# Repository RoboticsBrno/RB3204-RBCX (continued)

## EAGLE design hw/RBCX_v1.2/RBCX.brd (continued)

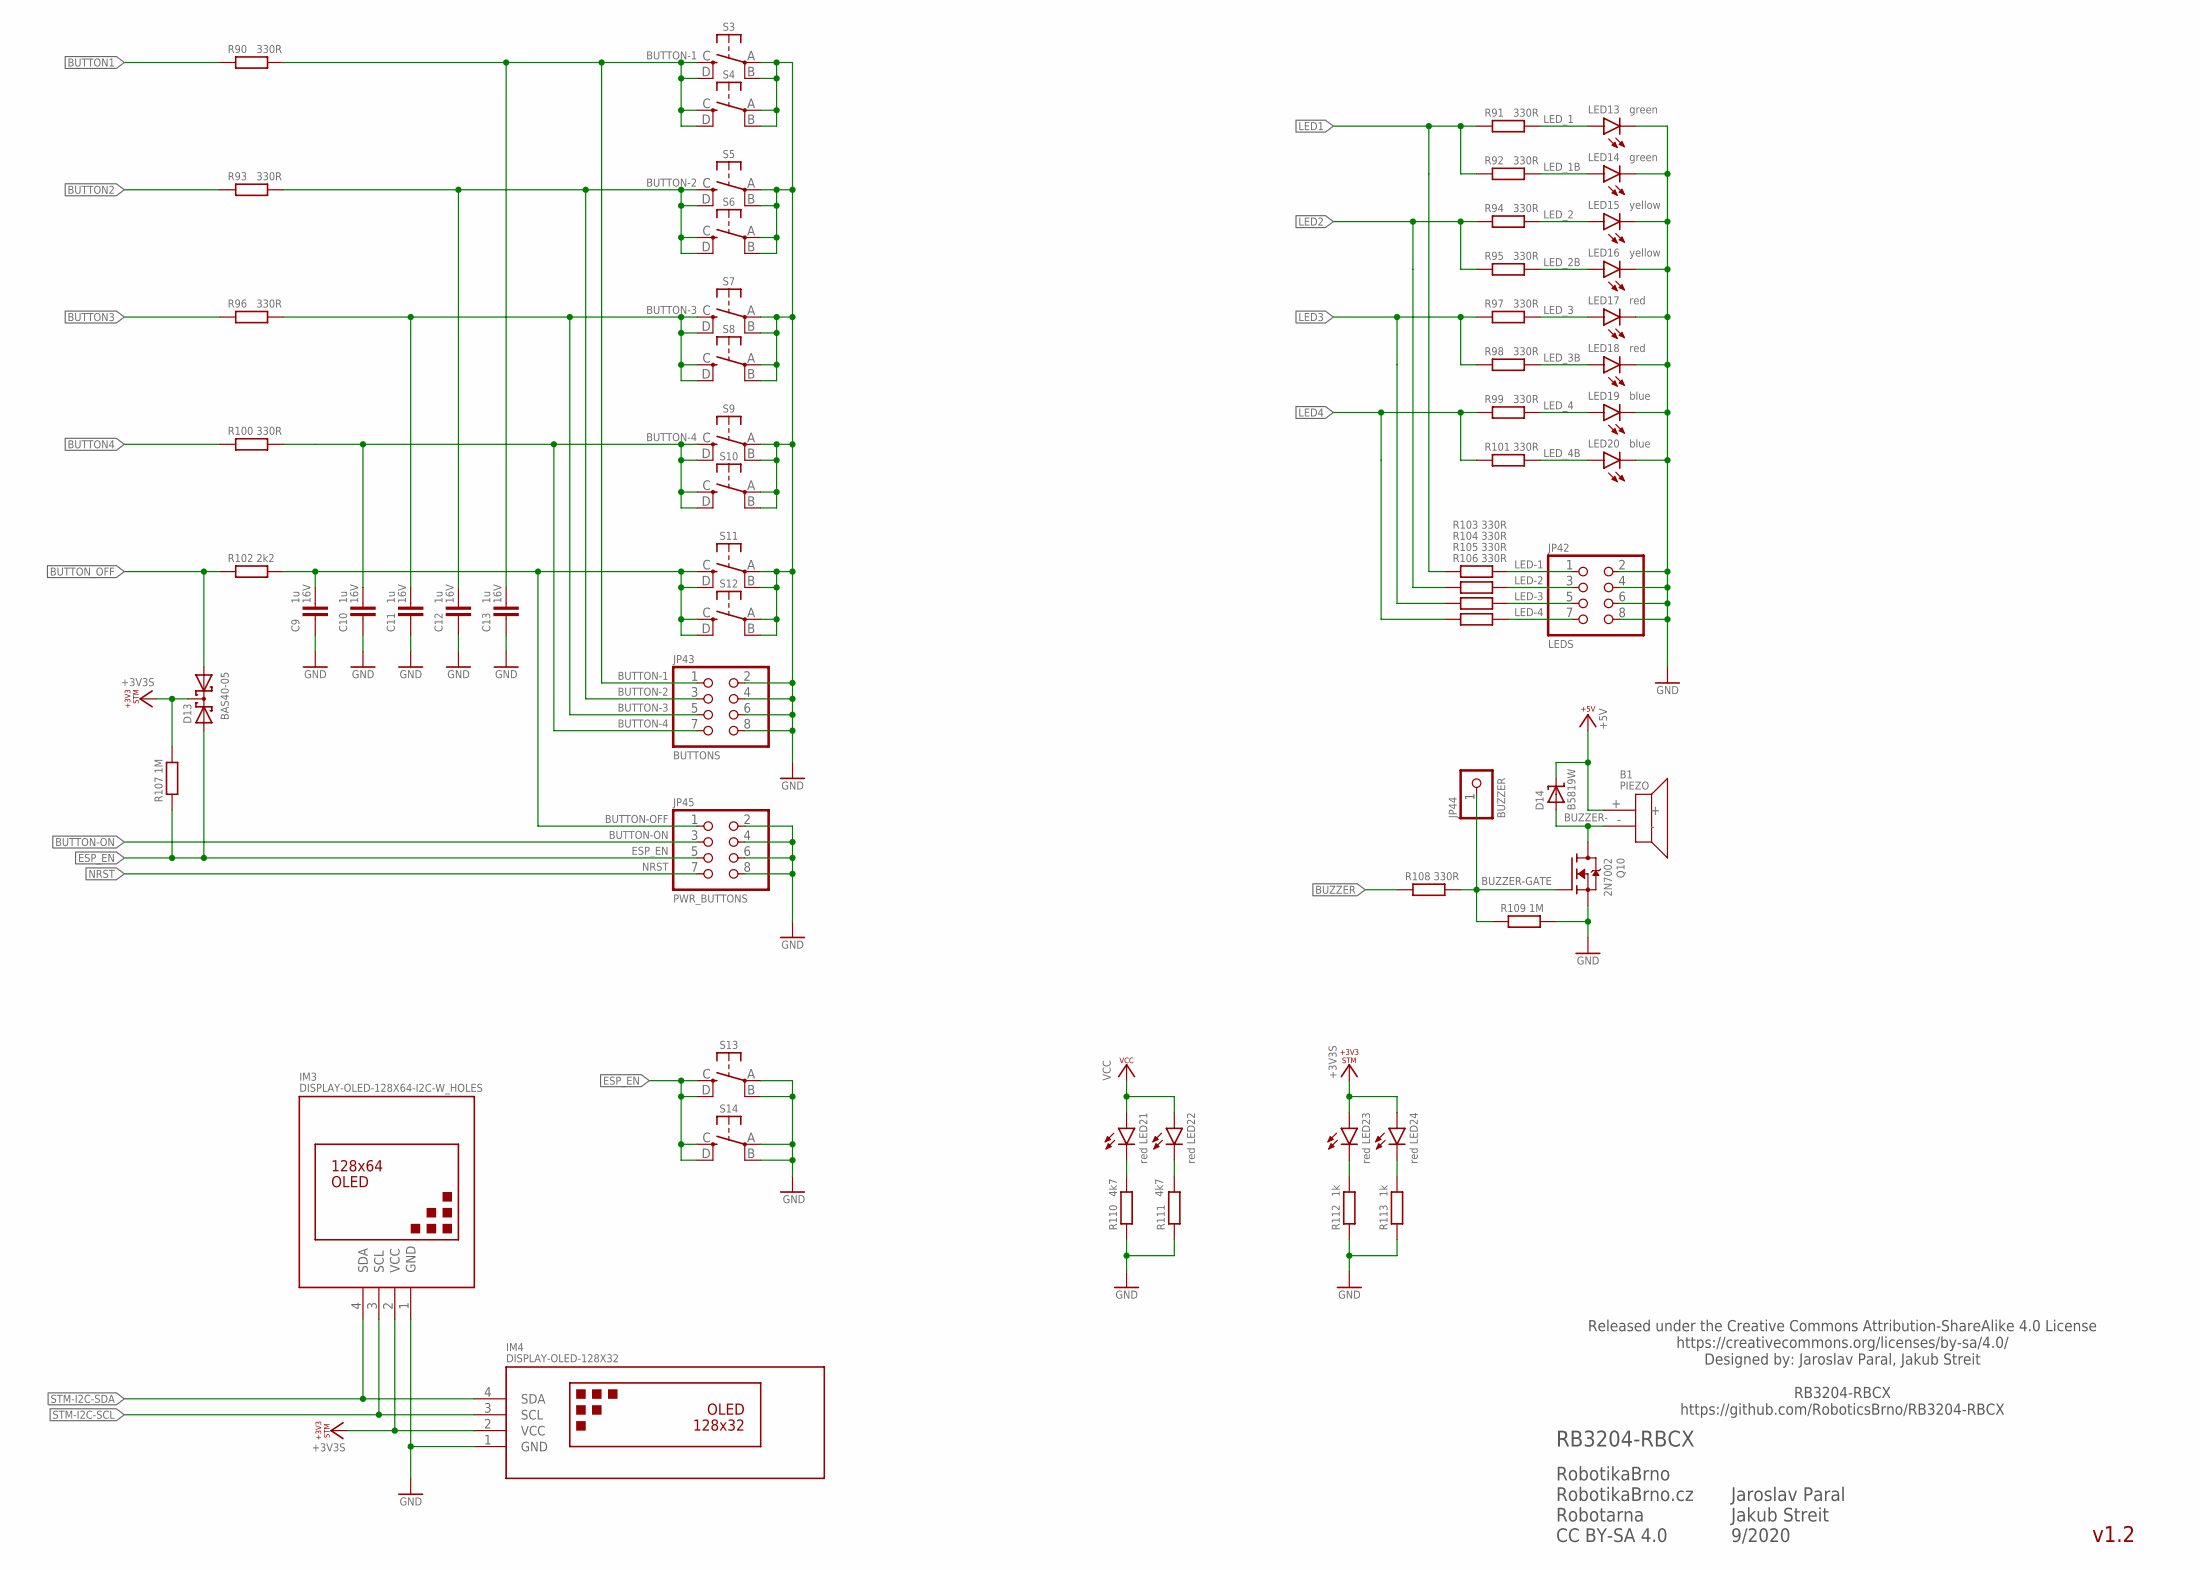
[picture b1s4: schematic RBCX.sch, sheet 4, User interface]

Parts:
B1: PIEZO
C9, C10, C11, C12, C13: 1u; C0402; VOLTAGE 16V
D13: BAS40-05; SOT23
D14: B5819W; SOD123; LCSC_ID C305445
IM3: DISPLAY-OLED-128X64-I2C-W_HOLES; DISPLAY-OLED-128X64-I2C_W-HOLES
IM4: DISPLAY-OLED-128X32
JP42: LEDS; 2X04
JP43: BUTTONS; 2X04
JP44: BUZZER; 1X01
JP45: PWR_BUTTONS; 2X04
LED13, LED14: green; CHIPLED_0603
LED15, LED16: yellow; CHIPLED_0603
LED17, LED18, LED21, LED22, LED23, LED24: red; CHIPLED_0603
LED19, LED20: blue; CHIPLED_0603
Q10: 2N7002; SOT23; LCSC_ID C8545
R90, R91, R92, R93, R94, R95, R96, R97, R98, R99, R100, R101, R103, R104, R105, R106, R108: 330R; R0402
R102: 2k2; R0402
R107, R109: 1M; R0402
R110, R111: 4k7; R0402
R112, R113: 1k; R0402
S3, S4, S5, S6, S7, S8, S9, S10, S11, S12, S13, S14: TS-1187A-C-C-B; TS-1187A

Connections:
+3V3S: D13.3 (C), IM3.2 (VCC), IM4.2 (VCC), LED23.A, LED24.A, R107.2; also elsewhere on the board
+5V: B1.+, D14.C; also elsewhere on the board
BUTTON1: R90.1; also elsewhere on the board
BUTTON2: R93.1; also elsewhere on the board
BUTTON3: R96.1; also elsewhere on the board
BUTTON4: R100.1; also elsewhere on the board
BUTTON-1: C13.1, JP43.1, R90.2, S3.C (S), S3.D (S1), S4.C (S), S4.D (S1); also elsewhere on the board
BUTTON-2: C12.1, JP43.3, R93.2, S5.C (S), S5.D (S1), S6.C (S), S6.D (S1); also elsewhere on the board
BUTTON-3: C11.1, JP43.5, R96.2, S7.C (S), S7.D (S1), S8.C (S), S8.D (S1); also elsewhere on the board
BUTTON-4: C10.1, JP43.7, R100.2, S9.C (S), S9.D (S1), S10.C (S), S10.D (S1); also elsewhere on the board
BUTTON-OFF: C9.1, JP45.1, R102.2, S11.C (S), S11.D (S1), S12.C (S), S12.D (S1); also elsewhere on the board
BUTTON-ON: JP45.3; also elsewhere on the board
BUTTON_OFF: D13.1 (A1), R102.1; also elsewhere on the board
BUZZER: R108.1; also elsewhere on the board
BUZZER-: B1.-, D14.A, Q10.3 (D)
BUZZER-GATE: JP44.1, Q10.1 (G), R108.2, R109.1; also elsewhere on the board
ESP_EN: D13.2 (A2), JP45.5, R107.1, S13.C (S), S13.D (S1), S14.C (S), S14.D (S1); also elsewhere on the board
GND: C9.2, C10.2, C11.2, C12.2, C13.2, IM3.1 (GND), IM4.1 (GND), JP42.2, JP42.4, JP42.6, JP42.8, JP43.2, JP43.4, JP43.6, JP43.8, JP45.2, JP45.4, JP45.6, JP45.8, LED13.C, LED14.C, LED15.C, LED16.C, LED17.C, LED18.C, LED19.C, LED20.C, Q10.2 (S), R109.2, R110.1, R111.1, R112.1, R113.1, S3.A, S3.B (P1), S4.A, S4.B (P1), S5.A, S5.B (P1), S6.A, S6.B (P1), S7.A, S7.B (P1), S8.A, S8.B (P1), S9.A, S9.B (P1), S10.A, S10.B (P1), S11.A, S11.B (P1), S12.A, S12.B (P1), S13.A, S13.B (P1), S14.A, S14.B (P1); also elsewhere on the board
LED1: R91.1, R92.1, R103.1; also elsewhere on the board
LED2: R94.1, R95.1, R104.1; also elsewhere on the board
LED3: R97.1, R98.1, R105.1; also elsewhere on the board
LED4: R99.1, R101.1, R106.1; also elsewhere on the board
LED-1: JP42.1, R103.2; also elsewhere on the board
LED-2: JP42.3, R104.2; also elsewhere on the board
LED-3: JP42.5, R105.2; also elsewhere on the board
LED-4: JP42.7, R106.2; also elsewhere on the board
LED_1: LED13.A, R91.2
LED_1B: LED14.A, R92.2
LED_2: LED15.A, R94.2
LED_2B: LED16.A, R95.2
LED_3: LED17.A, R97.2
LED_3B: LED18.A, R98.2
LED_4: LED19.A, R99.2
LED_4B: LED20.A, R101.2
NRST: JP45.7; also elsewhere on the board
PWRLED_+3V3S1: LED23.C, R112.2
PWRLED_+3V3S_B1: LED24.C, R113.2
PWRLED_VCC1: LED21.C, R110.2
PWRLED_VCC_B1: LED22.C, R111.2
STM-I2C-SCL: IM3.3 (SCL), IM4.3 (SCL); also elsewhere on the board
STM-I2C-SDA: IM3.4 (SDA), IM4.4 (SDA); also elsewhere on the board
VCC: LED21.A, LED22.A; also elsewhere on the board

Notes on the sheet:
v1.2
RobotikaBrno RobotikaBrno.cz Robotarna CC BY-SA 4.0
RB3204-RBCX
Released under the Creative Commons Attribution-ShareAlike 4.0 License https://creativecommons.org/licenses/by-sa/4.0/ Designed by: Jaroslav Paral, Jakub Streit RB3204-RBCX https://github.com/RoboticsBrno/RB3204-RBCX
Jaroslav Paral Jakub Streit 9/2020

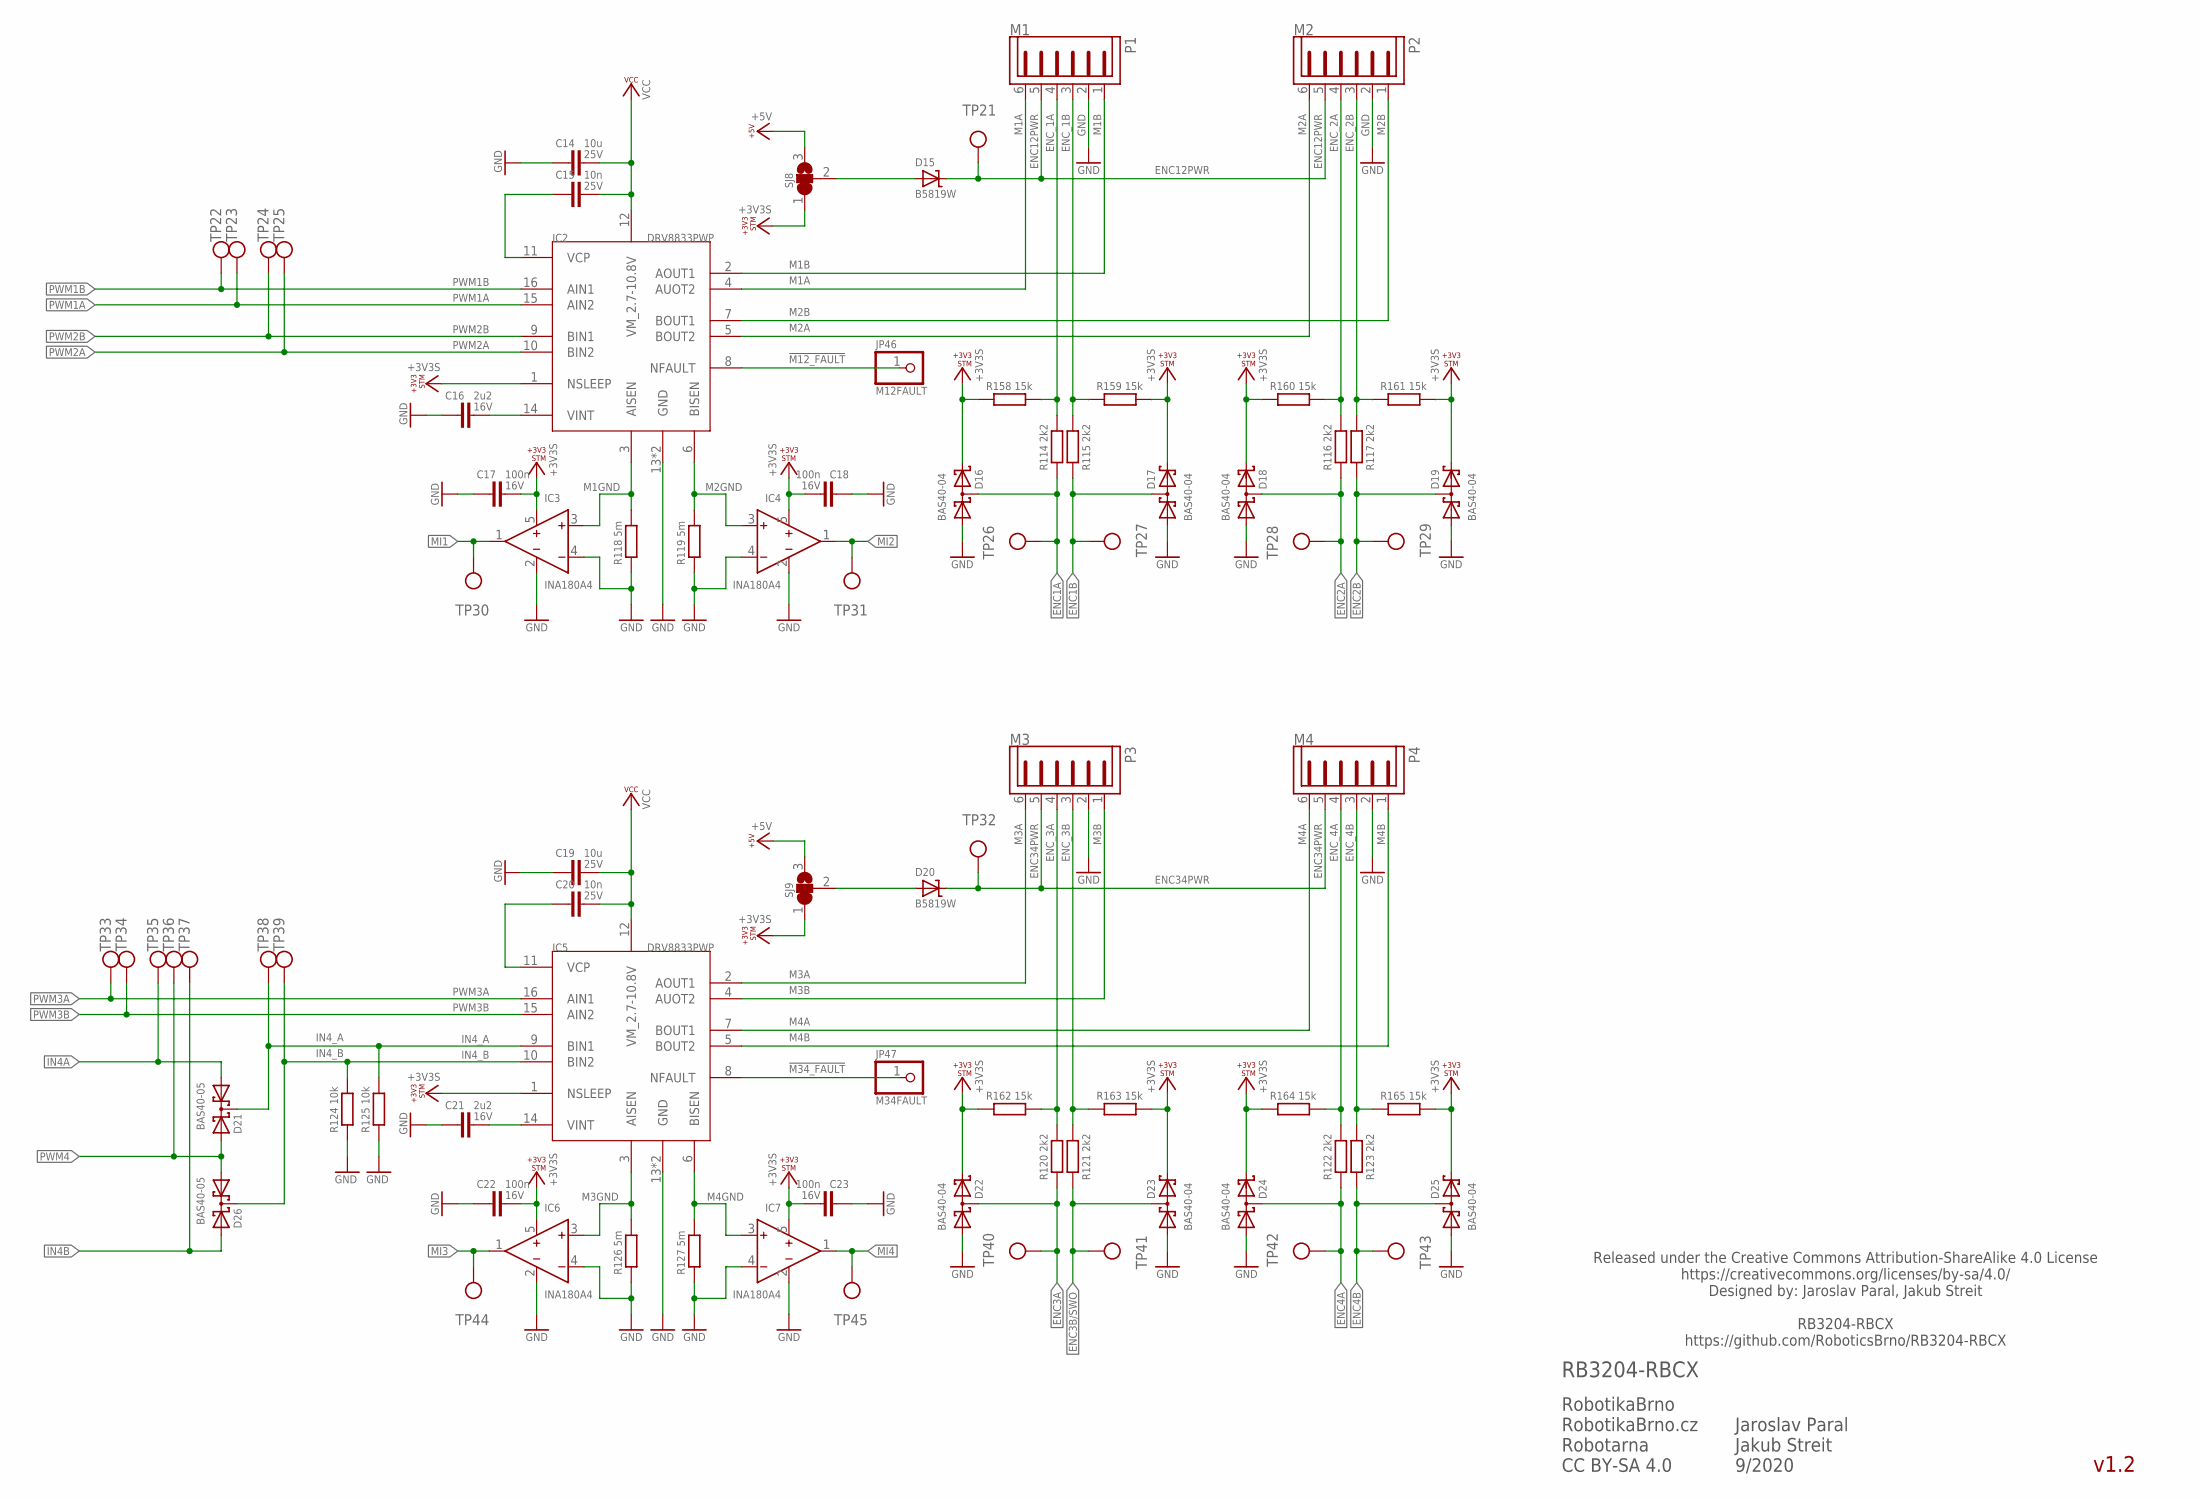
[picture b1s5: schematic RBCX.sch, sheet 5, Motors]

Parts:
C14, C19: 10u; C0805; VOLTAGE 25V
C15, C20: 10n; C0402; VOLTAGE 25V
C16, C21: 2u2; C0603; VOLTAGE 16V
C17, C18, C22, C23: 100n; C0402; VOLTAGE 16V
D15, D20: B5819W; SOD123; LCSC_ID C305445
D16, D17, D18, D19, D22, D23, D24, D25: BAS40-04; SOT23
D21, D26: BAS40-05; SOT23
IC2, IC5: DRV8833PWP; HTSSOP
IC3, IC4, IC6, IC7: INA180A4; SOT23-5L; LCSC_ID C133969
JP46: M12FAULT; 1X01
JP47: M34FAULT; 1X01
P1: M1; JST-PH6
P2: M2; JST-PH6
P3: M3; JST-PH6
P4: M4; JST-PH6
R114, R115, R116, R117, R120, R121, R122, R123: 2k2; R0402
R118, R119, R126, R127: 5m; R1206
R124, R125: 10k; R0402
R158, R159, R160, R161, R162, R163, R164, R165: 15k; R0402
SJ8, SJ9: SJ2W_DEFAULT; SJ_2_DEFAULT
TP21, TP22, TP23, TP24, TP25, TP26, TP27, TP28, TP29, TP30, TP31, TP32, TP33, TP34, TP35, TP36, TP37, TP38, TP39, TP40, TP41, TP42, TP43, TP44, TP45: TP_06MM; TP_06

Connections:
!M12_FAULT: IC2.8 (NFAULT), JP46.1
!M34_FAULT: IC5.8 (NFAULT), JP47.1
+3V3S: C17.1, C18.1, C22.1, C23.1, D16.2 (C2), D17.2 (C2), D18.2 (C2), D19.2 (C2), D22.2 (C2), D23.2 (C2), D24.2 (C2), D25.2 (C2), IC2.1 (NSLEEP), IC3.5 (VCC), IC4.5 (VCC), IC5.1 (NSLEEP), IC6.5 (VCC), IC7.5 (VCC), R158.1, R159.2, R160.1, R161.2, R162.1, R163.2, R164.1, R165.2, SJ8.1, SJ9.1; also elsewhere on the board
+5V: SJ8.3, SJ9.3; also elsewhere on the board
ENC1A: D16.3 (C1A2), R114.1, TP26.P$1; also elsewhere on the board
ENC1B: D17.3 (C1A2), R115.1, TP27.P$1; also elsewhere on the board
ENC2A: D18.3 (C1A2), R116.1, TP28.P$1; also elsewhere on the board
ENC2B: D19.3 (C1A2), R117.1, TP29.P$1; also elsewhere on the board
ENC3A: D22.3 (C1A2), R120.1, TP40.P$1; also elsewhere on the board
ENC3B/SWO: D23.3 (C1A2), R121.1, TP41.P$1; also elsewhere on the board
ENC4A: D24.3 (C1A2), R122.1, TP42.P$1; also elsewhere on the board
ENC4B: D25.3 (C1A2), R123.1, TP43.P$1; also elsewhere on the board
ENC12PWR: D15.C, P1.5, P2.5, TP21.P$1
ENC12_PWR: D15.A, SJ8.2
ENC34PWR: D20.C, P3.5, P4.5, TP32.P$1
ENC34_PWR: D20.A, SJ9.2
ENC_1A: P1.4, R114.2, R158.2
ENC_1B: P1.3, R115.2, R159.1
ENC_2A: P2.4, R116.2, R160.2
ENC_2B: P2.3, R117.2, R161.1
ENC_3A: P3.4, R120.2, R162.2
ENC_3B: P3.3, R121.2, R163.1
ENC_4A: P4.4, R122.2, R164.2
ENC_4B: P4.3, R123.2, R165.1
GND: C14.2, C16.2, C17.2, C18.2, C19.2, C21.2, C22.2, C23.2, D16.1 (A1), D17.1 (A1), D18.1 (A1), D19.1 (A1), D22.1 (A1), D23.1 (A1), D24.1 (A1), D25.1 (A1), IC2.13 (GND), IC2.GND, IC3.2 (GND), IC3.4 (IN-), IC4.2 (GND), IC4.4 (IN-), IC5.13 (GND), IC5.GND, IC6.2 (GND), IC6.4 (IN-), IC7.2 (GND), IC7.4 (IN-), P1.2, P2.2, P3.2, P4.2, R118.1, R119.1, R124.1, R125.1, R126.1, R127.1; also elsewhere on the board
IN4A: D21.1 (A1), TP35.P$1; also elsewhere on the board
IN4B: D26.2 (A2), TP37.P$1; also elsewhere on the board
IN4_A: D21.3 (C), IC5.9 (BIN1), R125.2, TP38.P$1
IN4_B: D26.3 (C), IC5.10 (BIN2), R124.2, TP39.P$1
M1A: IC2.4 (AUOT2), P1.6
M1B: IC2.2 (AOUT1), P1.1
M1GND: IC2.3 (AISEN), IC3.3 (IN+), R118.2
M2A: IC2.5 (BOUT2), P2.6
M2B: IC2.7 (BOUT1), P2.1
M2GND: IC2.6 (BISEN), IC4.3 (IN+), R119.2
M3A: IC5.2 (AOUT1), P3.6
M3B: IC5.4 (AUOT2), P3.1
M3GND: IC5.3 (AISEN), IC6.3 (IN+), R126.2
M4A: IC5.7 (BOUT1), P4.6
M4B: IC5.5 (BOUT2), P4.1
M4GND: IC5.6 (BISEN), IC7.3 (IN+), R127.2
MI1: IC3.1 (OUT), TP30.P$1; also elsewhere on the board
MI2: IC4.1 (OUT), TP31.P$1; also elsewhere on the board
MI3: IC6.1 (OUT), TP44.P$1; also elsewhere on the board
MI4: IC7.1 (OUT), TP45.P$1; also elsewhere on the board
PWM1A: IC2.15 (AIN2), TP23.P$1; also elsewhere on the board
PWM1B: IC2.16 (AIN1), TP22.P$1; also elsewhere on the board
PWM2A: IC2.10 (BIN2), TP25.P$1; also elsewhere on the board
PWM2B: IC2.9 (BIN1), TP24.P$1; also elsewhere on the board
PWM3A: IC5.16 (AIN1), TP33.P$1; also elsewhere on the board
PWM3B: IC5.15 (AIN2), TP34.P$1; also elsewhere on the board
PWM4: D21.2 (A2), D26.1 (A1), TP36.P$1; also elsewhere on the board
VCC: C14.1, C15.1, C19.1, C20.1, IC2.12 (VM_2.7-10.8V), IC5.12 (VM_2.7-10.8V); also elsewhere on the board
VCP12: C15.2, IC2.11 (VCP)
VCP34: C20.2, IC5.11 (VCP)
VINT12: C16.1, IC2.14 (VINT)
VINT34: C21.1, IC5.14 (VINT)

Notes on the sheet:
v1.2
RobotikaBrno RobotikaBrno.cz Robotarna CC BY-SA 4.0
RB3204-RBCX
Released under the Creative Commons Attribution-ShareAlike 4.0 License https://creativecommons.org/licenses/by-sa/4.0/ Designed by: Jaroslav Paral, Jakub Streit RB3204-RBCX https://github.com/RoboticsBrno/RB3204-RBCX
Jaroslav Paral Jakub Streit 9/2020

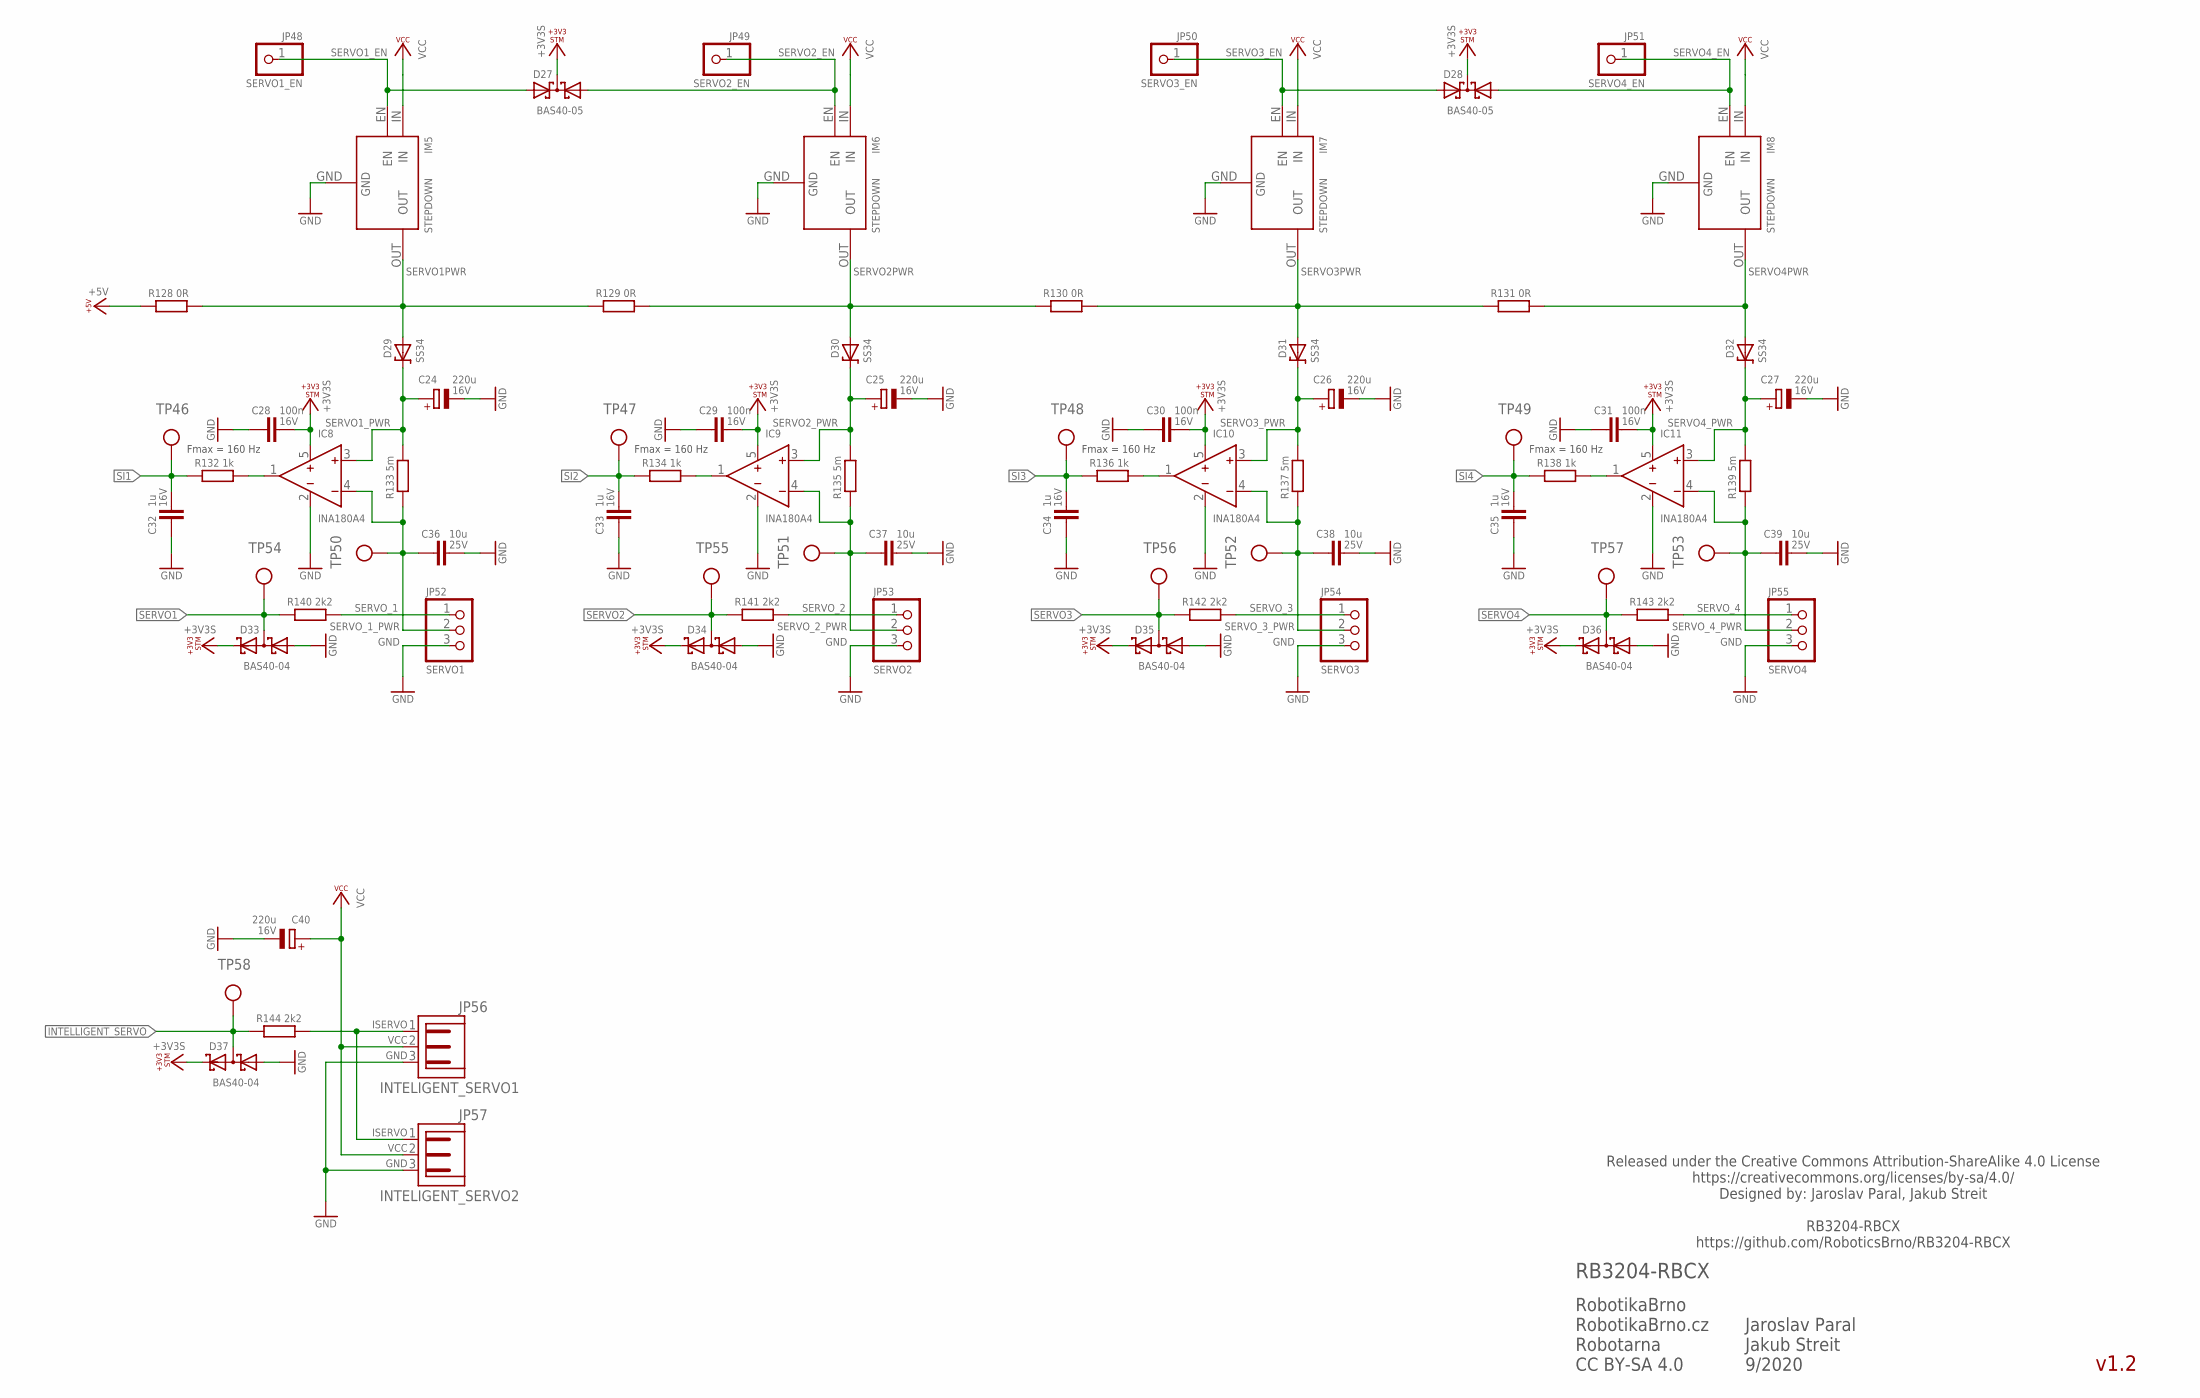
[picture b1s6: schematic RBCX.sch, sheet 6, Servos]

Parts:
C24, C25, C26, C27, C40: 220u; E5-10,5; VOLTAGE 16V
C28, C29, C30, C31: 100n; C0402; VOLTAGE 16V
C32, C33, C34, C35: 1u; C0402; VOLTAGE 16V
C36, C37, C38, C39: 10u; C0805; VOLTAGE 25V
D27, D28: BAS40-05; SOT23
D29, D30, D31, D32: SS34; SMA
D33, D34, D35, D36, D37: BAS40-04; SOT23
IC8, IC9, IC10, IC11: INA180A4; SOT23-5L; LCSC_ID C133969
IM5, IM6, IM7, IM8: STEPDOWN
JP48: SERVO1_EN; 1X01
JP49: SERVO2_EN; 1X01
JP50: SERVO3_EN; 1X01
JP51: SERVO4_EN; 1X01
JP52: SERVO1; 1X03
JP53: SERVO2; 1X03
JP54: SERVO3; 1X03
JP55: SERVO4; 1X03
JP56: INTELIGENT_SERVO1; JST-PH3
JP57: INTELIGENT_SERVO2; JST-PH3
R128, R129, R130, R131: 0R; R1206
R132, R134, R136, R138: 1k; R0402
R133, R135, R137, R139: 5m; R1206
R140, R141, R142, R143, R144: 2k2; R0402
TP46, TP47, TP48, TP49, TP50, TP51, TP52, TP53, TP54, TP55, TP56, TP57, TP58: TP_06MM; TP_06

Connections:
+3V3S: C28.1, C29.1, C30.1, C31.1, D27.3 (C), D28.3 (C), D33.2 (C2), D34.2 (C2), D35.2 (C2), D36.2 (C2), D37.2 (C2), IC8.5 (VCC), IC9.5 (VCC), IC10.5 (VCC), IC11.5 (VCC); also elsewhere on the board
+5V: R128.1; also elsewhere on the board
GND: C24.-, C25.-, C26.-, C27.-, C28.2, C29.2, C30.2, C31.2, C32.2, C33.2, C34.2, C35.2, C36.1, C37.1, C38.1, C39.1, C40.-, D33.1 (A1), D34.1 (A1), D35.1 (A1), D36.1 (A1), D37.1 (A1), IC8.2 (GND), IC9.2 (GND), IC10.2 (GND), IC11.2 (GND), IM5.GND, IM6.GND, IM7.GND, IM8.GND, JP52.3, JP53.3, JP54.3, JP55.3, JP56.3, JP57.3; also elsewhere on the board
INTELLIGENT_SERVO: D37.3 (C1A2), R144.1, TP58.P$1; also elsewhere on the board
ISERVO: JP56.1, JP57.1, R144.2
SERVO1: D33.3 (C1A2), R140.1, TP54.P$1; also elsewhere on the board
SERVO1PWR: D29.A, IM5.OUT, R128.2, R129.1
SERVO1_EN: D27.2 (A2), IM5.EN, JP48.1
SERVO1_PWR: C24.+, D29.C, IC8.3 (IN+), R133.2
SERVO2: D34.3 (C1A2), R141.1, TP55.P$1; also elsewhere on the board
SERVO2PWR: D30.A, IM6.OUT, R129.2, R130.1
SERVO2_EN: D27.1 (A1), IM6.EN, JP49.1
SERVO2_PWR: C25.+, D30.C, IC9.3 (IN+), R135.2
SERVO3: D35.3 (C1A2), R142.1, TP56.P$1; also elsewhere on the board
SERVO3PWR: D31.A, IM7.OUT, R130.2, R131.1
SERVO3_EN: D28.2 (A2), IM7.EN, JP50.1
SERVO3_PWR: C26.+, D31.C, IC10.3 (IN+), R137.2
SERVO4: D36.3 (C1A2), R143.1, TP57.P$1; also elsewhere on the board
SERVO4PWR: D32.A, IM8.OUT, R131.2
SERVO4_EN: D28.1 (A1), IM8.EN, JP51.1
SERVO4_PWR: C27.+, D32.C, IC11.3 (IN+), R139.2
SERVO_1: JP52.1, R140.2
SERVO_1_PWR: C36.2, IC8.4 (IN-), JP52.2, R133.1, TP50.P$1
SERVO_2: JP53.1, R141.2
SERVO_2_PWR: C37.2, IC9.4 (IN-), JP53.2, R135.1, TP51.P$1
SERVO_3: JP54.1, R142.2
SERVO_3_PWR: C38.2, IC10.4 (IN-), JP54.2, R137.1, TP52.P$1
SERVO_4: JP55.1, R143.2
SERVO_4_PWR: C39.2, IC11.4 (IN-), JP55.2, R139.1, TP53.P$1
SI1: C32.1, R132.1, TP46.P$1; also elsewhere on the board
SI2: C33.1, R134.1, TP47.P$1; also elsewhere on the board
SI3: C34.1, R136.1, TP48.P$1; also elsewhere on the board
SI4: C35.1, R138.1, TP49.P$1; also elsewhere on the board
SI_1: IC8.1 (OUT), R132.2
SI_2: IC9.1 (OUT), R134.2
SI_3: IC10.1 (OUT), R136.2
SI_4: IC11.1 (OUT), R138.2
VCC: C40.+, IM5.IN, IM6.IN, IM7.IN, IM8.IN, JP56.2, JP57.2; also elsewhere on the board

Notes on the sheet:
v1.2
RobotikaBrno RobotikaBrno.cz Robotarna CC BY-SA 4.0
RB3204-RBCX
Released under the Creative Commons Attribution-ShareAlike 4.0 License https://creativecommons.org/licenses/by-sa/4.0/ Designed by: Jaroslav Paral, Jakub Streit RB3204-RBCX https://github.com/RoboticsBrno/RB3204-RBCX
Jaroslav Paral Jakub Streit 9/2020
Fmax = 160 Hz

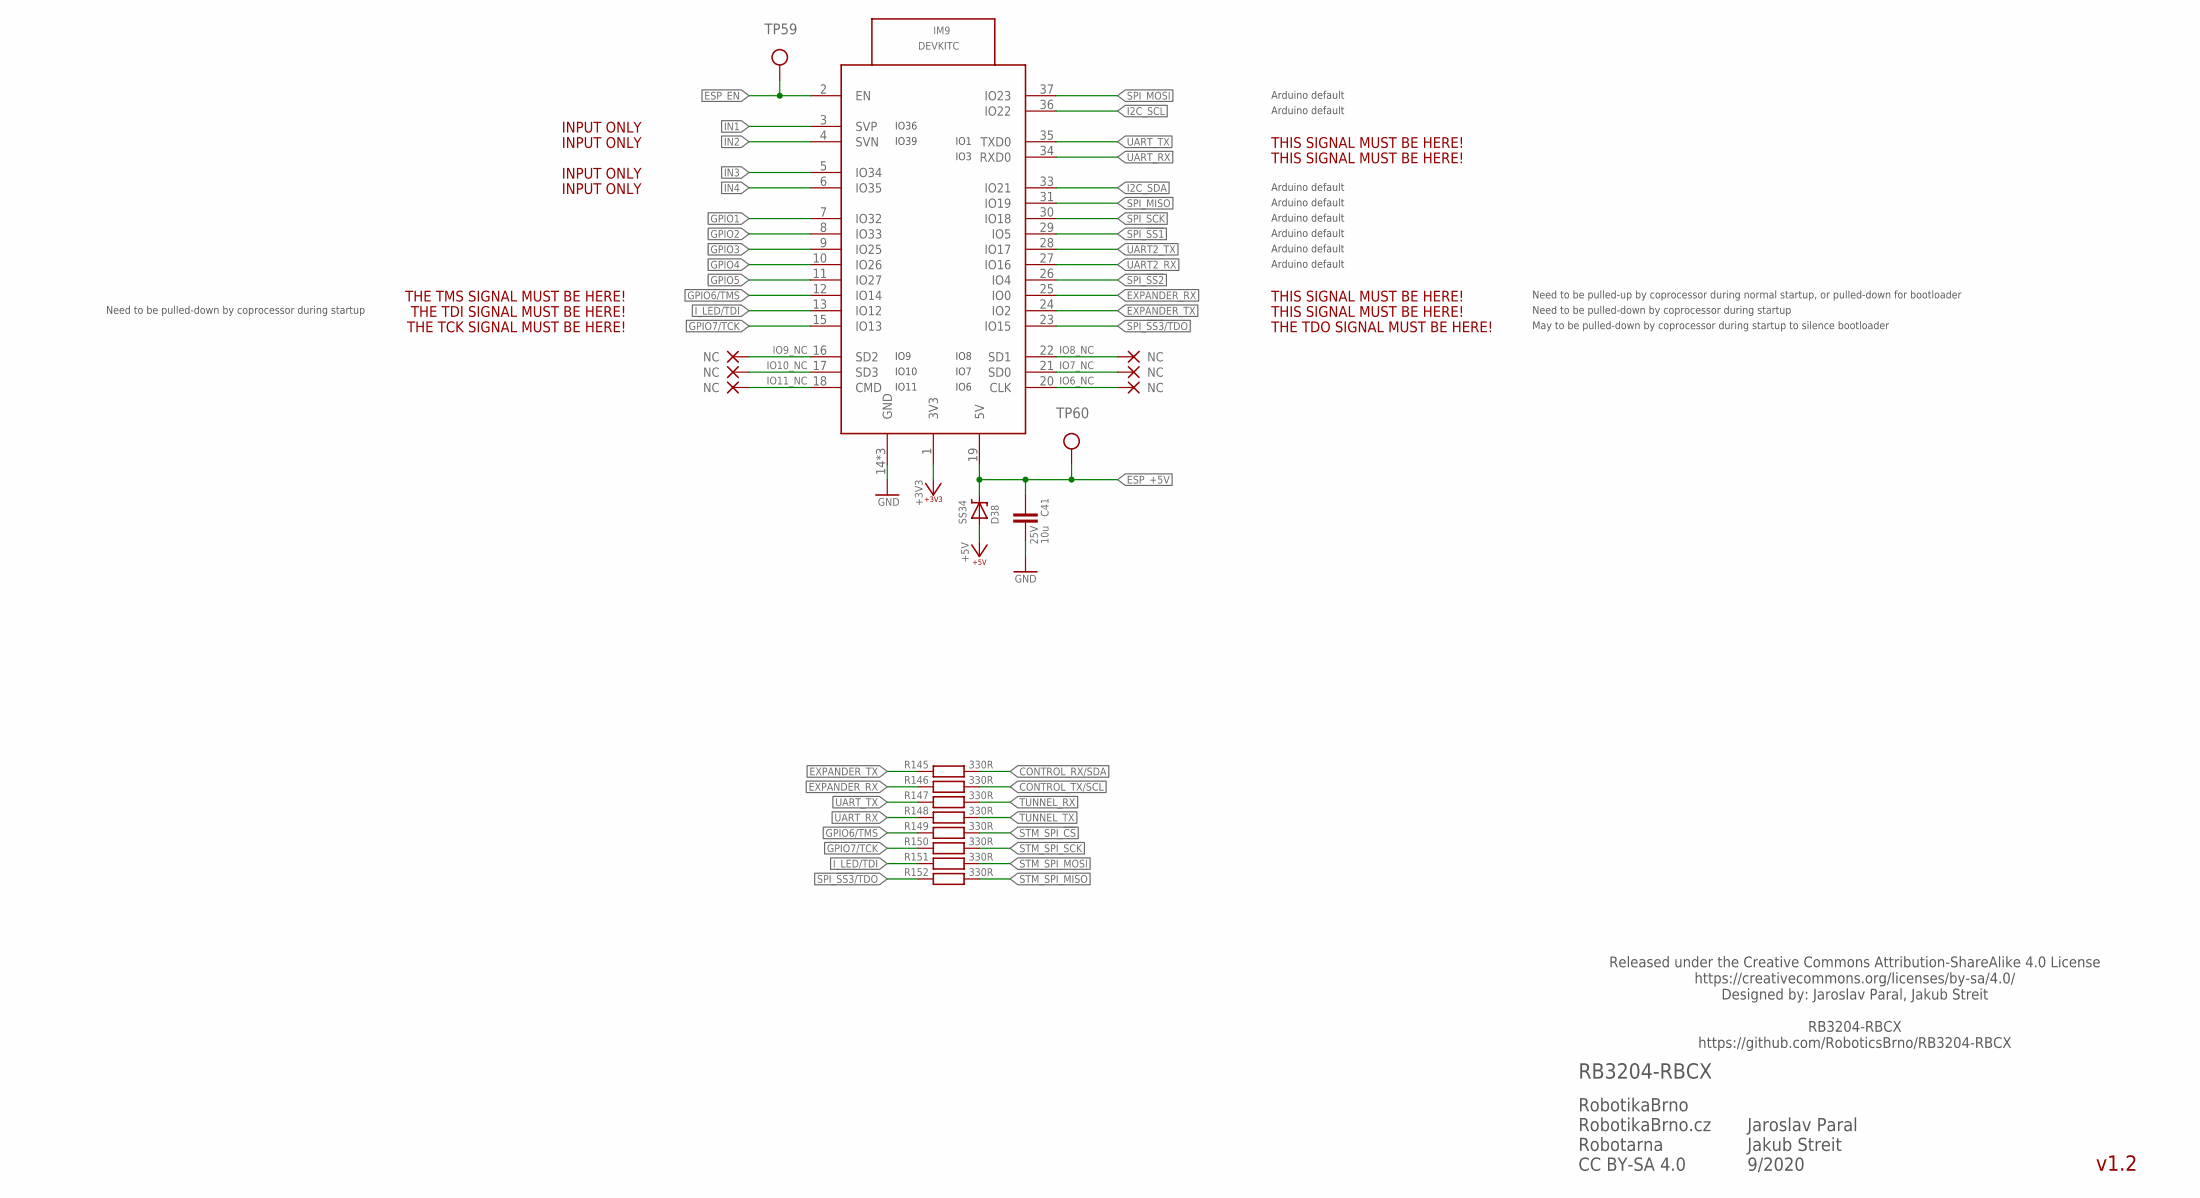
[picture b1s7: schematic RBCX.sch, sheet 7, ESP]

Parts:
C41: 10u; C0805; VOLTAGE 25V
D38: SS34; SMA
IM9: DEVKITC
R145, R146, R147, R148, R149, R150, R151, R152: 330R; R0402
TP59, TP60: TP_06MM; TP_06

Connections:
+3V3: IM9.1 (3V3); also elsewhere on the board
+5V: D38.A; also elsewhere on the board
CONTROL_RX/SDA: R145.2; also elsewhere on the board
CONTROL_TX/SCL: R146.2; also elsewhere on the board
ESP_+5V: C41.2, D38.C, IM9.19 (5V), TP60.P$1; also elsewhere on the board
ESP_EN: IM9.2 (EN), TP59.P$1; also elsewhere on the board
EXPANDER_RX: IM9.25 (IO0), R146.1
EXPANDER_TX: IM9.24 (IO2), R145.1
GND: C41.1, IM9.14 (GND), IM9.32 (GND), IM9.38 (GND); also elsewhere on the board
GPIO1: IM9.7 (IO32); also elsewhere on the board
GPIO2: IM9.8 (IO33); also elsewhere on the board
GPIO3: IM9.9 (IO25); also elsewhere on the board
GPIO4: IM9.10 (IO26); also elsewhere on the board
GPIO5: IM9.11 (IO27); also elsewhere on the board
GPIO6/TMS: IM9.12 (IO14), R149.1; also elsewhere on the board
GPIO7/TCK: IM9.15 (IO13), R150.1; also elsewhere on the board
I2C_SCL: IM9.36 (IO22); also elsewhere on the board
I2C_SDA: IM9.33 (IO21); also elsewhere on the board
IN1: IM9.3 (SVP); also elsewhere on the board
IN2: IM9.4 (SVN); also elsewhere on the board
IN3: IM9.5 (IO34); also elsewhere on the board
IN4: IM9.6 (IO35); also elsewhere on the board
IO6_NC: IM9.20 (CLK)
IO7_NC: IM9.21 (SD0)
IO8_NC: IM9.22 (SD1)
IO9_NC: IM9.16 (SD2)
IO10_NC: IM9.17 (SD3)
IO11_NC: IM9.18 (CMD)
I_LED/TDI: IM9.13 (IO12), R151.1; also elsewhere on the board
SPI_!SS1: IM9.29 (IO5); also elsewhere on the board
SPI_!SS2: IM9.26 (IO4); also elsewhere on the board
SPI_!SS3!/TDO: IM9.23 (IO15), R152.1; also elsewhere on the board
SPI_MISO: IM9.31 (IO19); also elsewhere on the board
SPI_MOSI: IM9.37 (IO23); also elsewhere on the board
SPI_SCK: IM9.30 (IO18); also elsewhere on the board
STM_SPI_!CS: R149.2; also elsewhere on the board
STM_SPI_MISO: R152.2; also elsewhere on the board
STM_SPI_MOSI: R151.2; also elsewhere on the board
STM_SPI_SCK: R150.2; also elsewhere on the board
TUNNEL_RX: R147.2; also elsewhere on the board
TUNNEL_TX: R148.2; also elsewhere on the board
UART2_RX: IM9.27 (IO16); also elsewhere on the board
UART2_TX: IM9.28 (IO17); also elsewhere on the board
UART_RX: IM9.34 (RXD0), R148.1; also elsewhere on the board
UART_TX: IM9.35 (TXD0), R147.1; also elsewhere on the board

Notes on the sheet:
THE TDI SIGNAL MUST BE HERE!
v1.2
RobotikaBrno RobotikaBrno.cz Robotarna CC BY-SA 4.0
RB3204-RBCX
Released under the Creative Commons Attribution-ShareAlike 4.0 License https://creativecommons.org/licenses/by-sa/4.0/ Designed by: Jaroslav Paral, Jakub Streit RB3204-RBCX https://github.com/RoboticsBrno/RB3204-RBCX
Jaroslav Paral Jakub Streit 9/2020
THIS SIGNAL MUST BE HERE!
INPUT ONLY
Arduino default
THE TCK SIGNAL MUST BE HERE!
THE TDO SIGNAL MUST BE HERE!
THE TMS SIGNAL MUST BE HERE!
Need to be pulled-up by coprocessor during normal startup, or pulled-down for bootloader
Need to be pulled-down by coprocessor during startup
May to be pulled-down by coprocessor during startup to silence bootloader
